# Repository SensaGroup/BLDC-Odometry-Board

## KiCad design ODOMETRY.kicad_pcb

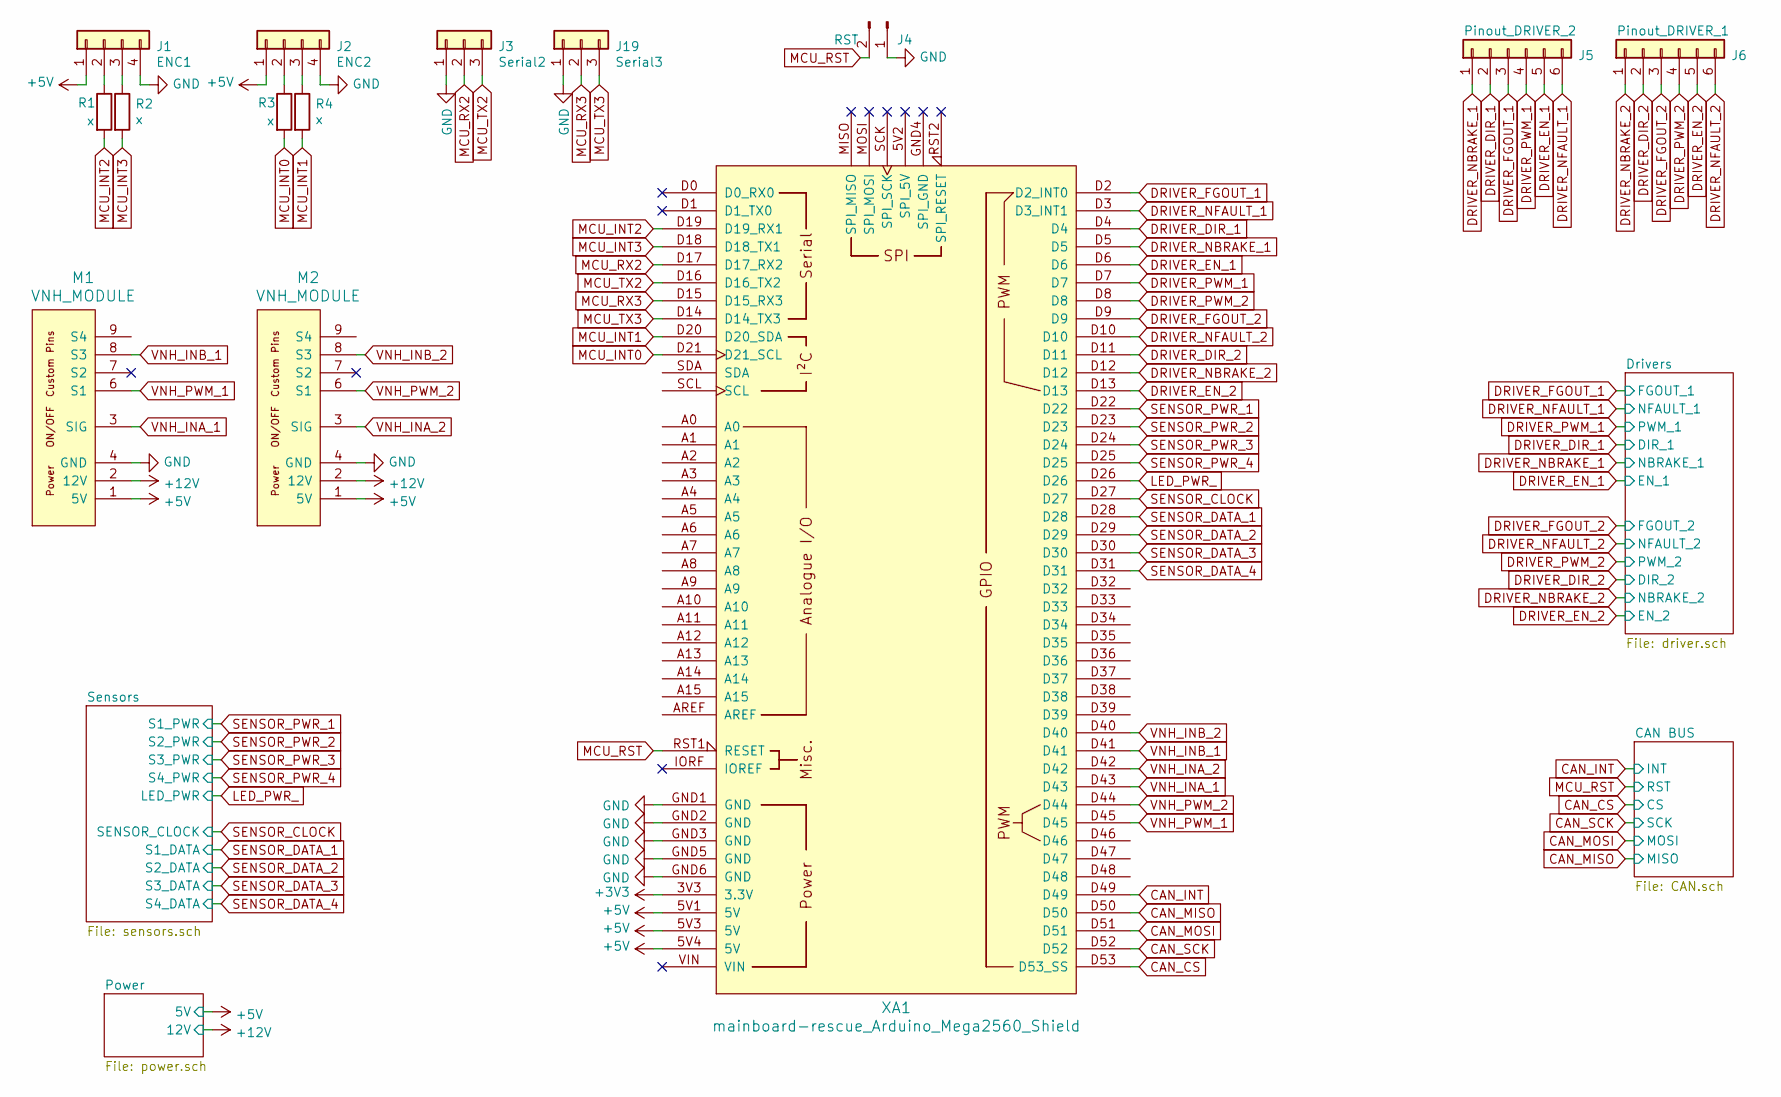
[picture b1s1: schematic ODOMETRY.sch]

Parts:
J1: ENC1; PinHeader_1x04_P2.54mm_Vertical
J2: ENC2; PinHeader_1x04_P2.54mm_Vertical
J3: Serial2; JST_PH_B3B-PH-K_1x03_P2.00mm_Vertical
J4: RST; PinHeader_1x02_P2.00mm_Vertical
J5: Pinout_DRIVER_2; PinHeader_1x06_P2.00mm_Vertical
J6: Pinout_DRIVER_1; PinHeader_1x06_P2.00mm_Vertical
J19: Serial3; JST_PH_B3B-PH-K_1x03_P2.00mm_Vertical
M1, M2: VNH_MODULE; Aktuator_Module
R1, R2, R3, R4: x; R_0603_1608Metric
XA1: mainboard-rescue_Arduino_Mega2560_Shield; Arduino_Mega2560_Shield

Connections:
+3V3: XA1.3V3 (3.3V)
+5V: J1.1, J2.1, M1.1 (5V), M2.1 (5V), XA1.5V1 (5V), XA1.5V3 (5V), XA1.5V4 (5V); also elsewhere on the board
CAN_CS: XA1.D53 (D53_SS); also elsewhere on the board
CAN_INT: XA1.D49; also elsewhere on the board
CAN_MISO: XA1.D50; also elsewhere on the board
CAN_MOSI: XA1.D51; also elsewhere on the board
CAN_SCK: XA1.D52; also elsewhere on the board
DIR_1: J5.2, XA1.D4; also elsewhere on the board
DIR_2: J6.2, XA1.D11; also elsewhere on the board
DRIVER_EN_1: J5.5, XA1.D6; also elsewhere on the board
DRIVER_EN_2: J6.5, XA1.D13; also elsewhere on the board
DRIVER_FGOUT_1: J5.3, XA1.D2 (D2_INT0); also elsewhere on the board
DRIVER_FGOUT_2: J6.3, XA1.D9; also elsewhere on the board
DRIVER_NBRAKE_1: J5.1, XA1.D5; also elsewhere on the board
DRIVER_NBRAKE_2: J6.1, XA1.D12; also elsewhere on the board
DRIVER_NFAULT_1: J5.6, XA1.D3 (D3_INT1); also elsewhere on the board
DRIVER_NFAULT_2: J6.6, XA1.D10; also elsewhere on the board
DRIVER_PWM_1: J5.4, XA1.D7; also elsewhere on the board
DRIVER_PWM_2: J6.4, XA1.D8; also elsewhere on the board
GND: J1.4, J2.4, J3.1, J4.1, J19.1, M1.4 (GND), M2.4 (GND), XA1.GND1 (GND), XA1.GND2 (GND), XA1.GND3 (GND), XA1.GND5 (GND), XA1.GND6 (GND); also elsewhere on the board
LED_PWR_: XA1.D26; also elsewhere on the board
MCU_INT0: R3.2, XA1.D21 (D21_SCL)
MCU_INT1: R4.2, XA1.D20 (D20_SDA)
MCU_INT2: R1.2, XA1.D19 (D19_RX1)
MCU_INT3: R2.2, XA1.D18 (D18_TX1)
MCU_RST: J4.2, XA1.RST1 (RESET); also elsewhere on the board
MCU_RX2: J3.2, XA1.D17 (D17_RX2)
MCU_RX3: J19.2, XA1.D15 (D15_RX3)
MCU_TX2: J3.3, XA1.D16 (D16_TX2)
MCU_TX3: J19.3, XA1.D14 (D14_TX3)
unnamed: J1.2, R1.1
unnamed: J1.3, R2.1
unnamed: J2.2, R3.1
unnamed: J2.3, R4.1
SENSOR_CLOCK: XA1.D27; also elsewhere on the board
SENSOR_DATA_1: XA1.D28; also elsewhere on the board
SENSOR_DATA_2: XA1.D29; also elsewhere on the board
SENSOR_DATA_3: XA1.D30; also elsewhere on the board
SENSOR_DATA_4: XA1.D31; also elsewhere on the board
SENSOR_PWR_1: XA1.D22; also elsewhere on the board
SENSOR_PWR_2: XA1.D23; also elsewhere on the board
SENSOR_PWR_3: XA1.D24; also elsewhere on the board
SENSOR_PWR_4: XA1.D25; also elsewhere on the board
VDRAIN_1: M1.2 (12V), M2.2 (12V); also elsewhere on the board
VNH_INA_1: M1.3 (SIG), XA1.D43
VNH_INA_2: M2.3 (SIG), XA1.D42
VNH_INB_1: M1.8 (S3), XA1.D41
VNH_INB_2: M2.8 (S3), XA1.D40
VNH_PWM_1: M1.6 (S1), XA1.D45
VNH_PWM_2: M2.6 (S1), XA1.D44

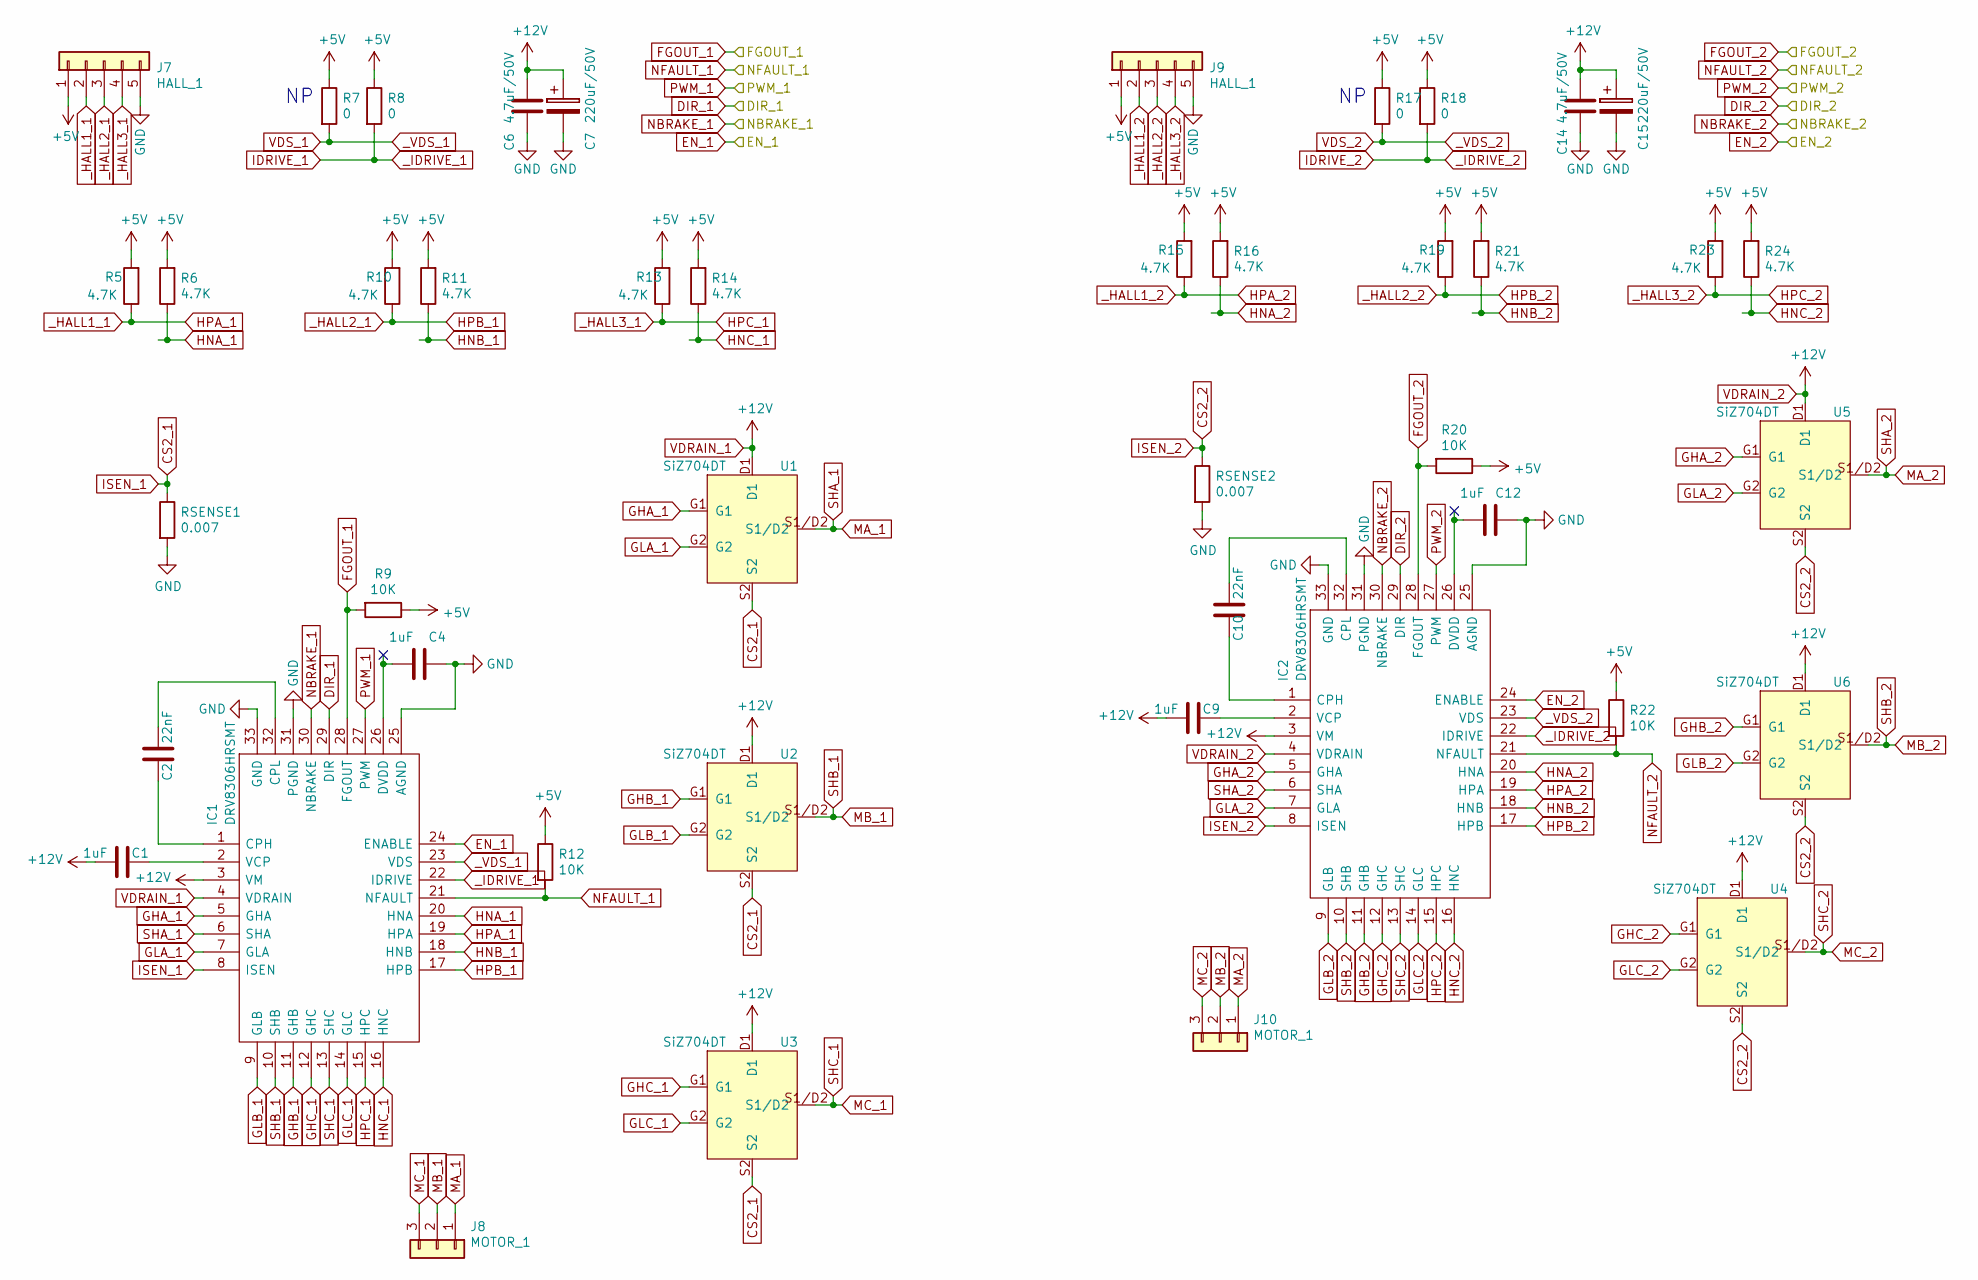
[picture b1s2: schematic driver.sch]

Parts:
C1, C4, C9, C12: 1uF; C_0603_1608Metric
C2, C10: 22nF; C_0603_1608Metric
C6, C14: 4.7uF/50V; C_1206_3216Metric
C7, C15: 220uF/50V; C_Elec_10x10.2
IC1, IC2: DRV8306HRSMT; QFN40P400X400X100-33N-D; Manufacturer_Part_Number DRV8306HRSMT; Mouser Part Number 595-DRV8306HRSMT
J7, J9: HALL_1; PinHeader_1x05_P2.54mm_Vertical
J8, J10: MOTOR_1; TerminalBlock_Phoenix_MKDS-1,5-3_1x03_P5.00mm_Horizontal
R5, R6, R10, R11, R13, R14, R15, R16, R19, R21, R23, R24: 4.7K; R_0603_1608Metric
R7, R8, R17, R18: 0; R_0603_1608Metric
R9, R12, R20, R22: 10K; R_0603_1608Metric
RSENSE1, RSENSE2: 0.007; R_2512_6332Metric
U1, U2, U3, U4, U5, U6: SiZ704DT

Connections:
+5V: J7.1, J9.1, R5.2, R6.2, R7.1, R8.1, R9.1, R10.2, R11.2, R12.1, R13.2, R14.2, R15.2, R16.2, R17.1, R18.1, R19.2, R20.1, R21.2, R22.1, R23.2, R24.2; also elsewhere on the board
CS2_1: IC1.8 (ISEN), RSENSE1.1, U1.S2, U2.S2, U3.S2
CS2_2: IC2.8 (ISEN), RSENSE2.1, U4.S2, U5.S2, U6.S2
DIR_1: IC1.29 (DIR); also elsewhere on the board
DIR_2: IC2.29 (DIR); also elsewhere on the board
DRIVER_EN_1: IC1.24 (ENABLE); also elsewhere on the board
DRIVER_EN_2: IC2.24 (ENABLE); also elsewhere on the board
DRIVER_FGOUT_1: IC1.28 (FGOUT), R9.2; also elsewhere on the board
DRIVER_FGOUT_2: IC2.28 (FGOUT), R20.2; also elsewhere on the board
DRIVER_NBRAKE_1: IC1.30 (NBRAKE); also elsewhere on the board
DRIVER_NBRAKE_2: IC2.30 (NBRAKE); also elsewhere on the board
DRIVER_NFAULT_1: IC1.21 (NFAULT), R12.2; also elsewhere on the board
DRIVER_NFAULT_2: IC2.21 (NFAULT), R22.2; also elsewhere on the board
DRIVER_PWM_1: IC1.27 (PWM); also elsewhere on the board
DRIVER_PWM_2: IC2.27 (PWM); also elsewhere on the board
GHA_1: IC1.5 (GHA), U1.G1
GHA_2: IC2.5 (GHA), U5.G1
GHB_1: IC1.11 (GHB), U2.G1
GHB_2: IC2.11 (GHB), U6.G1
GHC_1: IC1.12 (GHC), U3.G1
GHC_2: IC2.12 (GHC), U4.G1
GLA_1: IC1.7 (GLA), U1.G2
GLA_2: IC2.7 (GLA), U5.G2
GLB_1: IC1.9 (GLB), U2.G2
GLB_2: IC2.9 (GLB), U6.G2
GLC_1: IC1.14 (GLC), U3.G2
GLC_2: IC2.14 (GLC), U4.G2
GND: C4.1, C6.1, C7.2, C12.1, C14.1, C15.2, IC1.25 (AGND), IC1.31 (PGND), IC1.33 (GND), IC2.25 (AGND), IC2.31 (PGND), IC2.33 (GND), J7.5, J9.5, RSENSE1.2, RSENSE2.2; also elsewhere on the board
HNA_1: IC1.20 (HNA), R6.1
HNA_2: IC2.20 (HNA), R16.1
HNB_1: IC1.18 (HNB), R11.1
HNB_2: IC2.18 (HNB), R21.1
HNC_1: IC1.16 (HNC), R14.1
HNC_2: IC2.16 (HNC), R24.1
HPA_1: IC1.19 (HPA), J7.2, R5.1
HPA_2: IC2.19 (HPA), J9.2, R15.1
HPB_1: IC1.17 (HPB), J7.3, R10.1
HPB_2: IC2.17 (HPB), J9.3, R19.1
HPC_1: IC1.15 (HPC), J7.4, R13.1
HPC_2: IC2.15 (HPC), J9.4, R23.1
IDRIVE_1: IC1.22 (IDRIVE), R8.2
IDRIVE_2: IC2.22 (IDRIVE), R18.2
MA_1: IC1.6 (SHA), J8.1, U1.S1/D2
MA_2: IC2.6 (SHA), J10.1, U5.S1/D2
MB_1: IC1.10 (SHB), J8.2, U2.S1/D2
MB_2: IC2.10 (SHB), J10.2, U6.S1/D2
MC_1: IC1.13 (SHC), J8.3, U3.S1/D2
MC_2: IC2.13 (SHC), J10.3, U4.S1/D2
unnamed: C1.1, IC1.2 (VCP)
unnamed: C2.1, IC1.1 (CPH)
unnamed: C2.2, IC1.32 (CPL)
unnamed: C4.2, IC1.26 (DVDD)
unnamed: C9.1, IC2.2 (VCP)
unnamed: C10.1, IC2.1 (CPH)
unnamed: C10.2, IC2.32 (CPL)
unnamed: C12.2, IC2.26 (DVDD)
VDRAIN_1: C1.2, C6.2, C7.1, C9.2, C14.2, C15.1, IC1.3 (VM), IC1.4 (VDRAIN), IC2.3 (VM), IC2.4 (VDRAIN), U1.D1, U2.D1, U3.D1, U4.D1, U5.D1, U6.D1; also elsewhere on the board
VDS_1: IC1.23 (VDS), R7.2
VDS_2: IC2.23 (VDS), R17.2

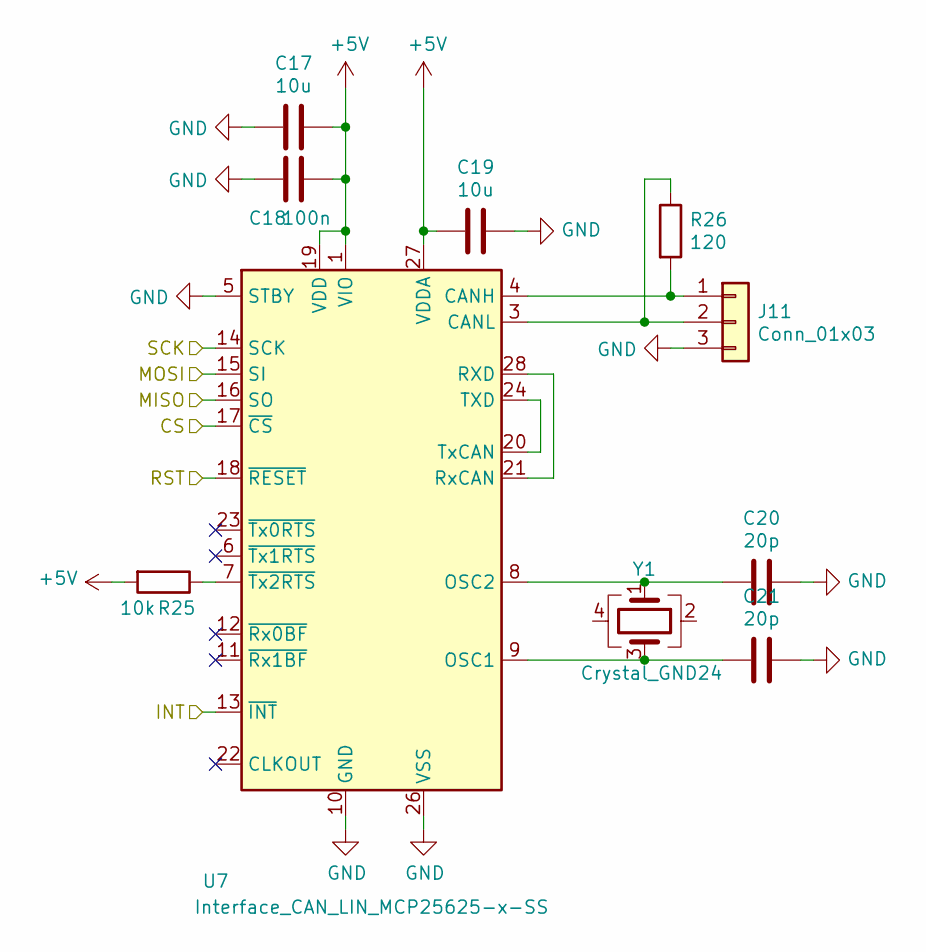
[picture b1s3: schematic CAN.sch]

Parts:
C17, C19: 10u; C_0603_1608Metric
C18: 100n; C_0603_1608Metric
C20, C21: 20p; C_0603_1608Metric
J11: Conn_01x03; JST_PH_B3B-PH-K_1x03_P2.00mm_Vertical
R25: 10k; R_0603_1608Metric
R26: 120; R_0603_1608Metric
U7: Interface_CAN_LIN_MCP25625-x-SS; SSOP-28_5.3x10.2mm_P0.65mm
Y1: Crystal_GND24; Crystal_SMD_SeikoEpson_FA238-4Pin_3.2x2.5mm_HandSoldering

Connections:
+5V: C17.1, C18.1, C19.1, R25.2, U7.1 (VIO), U7.19 (VDD), U7.27 (VDDA); also elsewhere on the board
CAN_CS: U7.17 (~CS); also elsewhere on the board
CAN_INT: U7.13 (~INT); also elsewhere on the board
CAN_MISO: U7.16 (SO); also elsewhere on the board
CAN_MOSI: U7.15 (SI); also elsewhere on the board
CAN_SCK: U7.14 (SCK); also elsewhere on the board
GND: C17.2, C18.2, C19.2, C20.2, C21.2, J11.3, U7.5 (STBY), U7.10 (GND), U7.26 (VSS); also elsewhere on the board
MCU_RST: U7.18 (~RESET); also elsewhere on the board
unnamed: C20.1, U7.8 (OSC2), Y1.1
unnamed: C21.1, U7.9 (OSC1), Y1.3
unnamed: J11.1, R26.2, U7.4 (CANH)
unnamed: J11.2, R26.1, U7.3 (CANL)
unnamed: R25.1, U7.7 (~Tx2RTS)
unnamed: U7.20 (TxCAN), U7.24 (TXD)
unnamed: U7.21 (RxCAN), U7.28 (RXD)

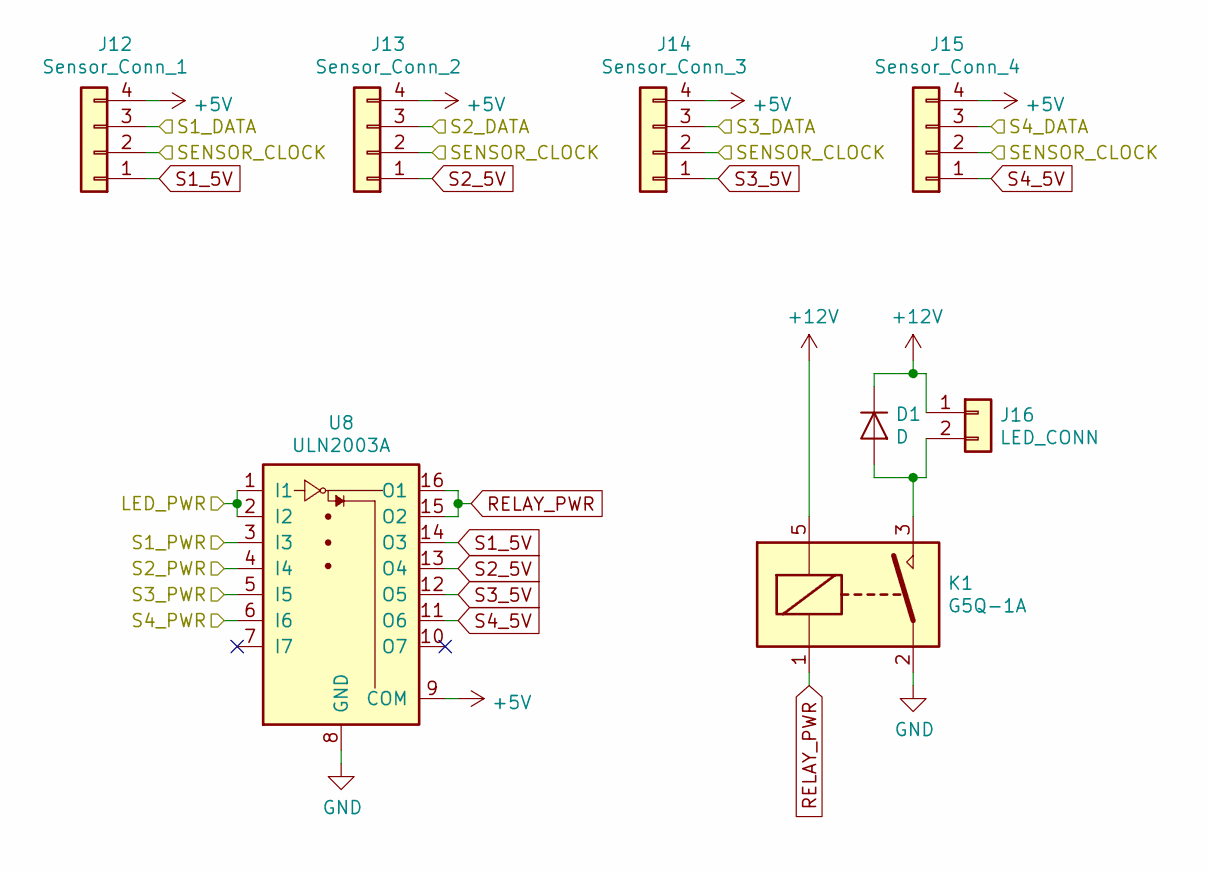
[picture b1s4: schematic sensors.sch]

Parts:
D1: D; D_SMA
J12: Sensor_Conn_1; JST_PH_B4B-PH-K_1x04_P2.00mm_Vertical
J13: Sensor_Conn_2; JST_PH_B4B-PH-K_1x04_P2.00mm_Vertical
J14: Sensor_Conn_3; JST_PH_B4B-PH-K_1x04_P2.00mm_Vertical
J15: Sensor_Conn_4; JST_PH_B4B-PH-K_1x04_P2.00mm_Vertical
J16: LED_CONN; JST_PH_B2B-PH-K_1x02_P2.00mm_Vertical
K1: G5Q-1A; Relay_SPST_Omron-G5Q-1A
U8: ULN2003A; TSSOP-16-1EP_4.4x5mm_P0.65mm

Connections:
+5V: J12.4, J13.4, J14.4, J15.4, U8.9 (COM); also elsewhere on the board
GND: K1.2, U8.8 (GND); also elsewhere on the board
LED_PWR_: U8.1 (I1), U8.2 (I2); also elsewhere on the board
unnamed: D1.2 (A), J16.2, K1.3
RELAY_PWR: K1.1, U8.15 (O2), U8.16 (O1)
S1_5V: J12.1, U8.14 (O3)
S2_5V: J13.1, U8.13 (O4)
S3_5V: J14.1, U8.12 (O5)
S4_5V: J15.1, U8.11 (O6)
SENSOR_CLOCK: J12.2, J13.2, J14.2, J15.2; also elsewhere on the board
SENSOR_DATA_1: J12.3; also elsewhere on the board
SENSOR_DATA_2: J13.3; also elsewhere on the board
SENSOR_DATA_3: J14.3; also elsewhere on the board
SENSOR_DATA_4: J15.3; also elsewhere on the board
SENSOR_PWR_1: U8.3 (I3); also elsewhere on the board
SENSOR_PWR_2: U8.4 (I4); also elsewhere on the board
SENSOR_PWR_3: U8.5 (I5); also elsewhere on the board
SENSOR_PWR_4: U8.6 (I6); also elsewhere on the board
VDRAIN_1: D1.1 (K), J16.1, K1.5; also elsewhere on the board

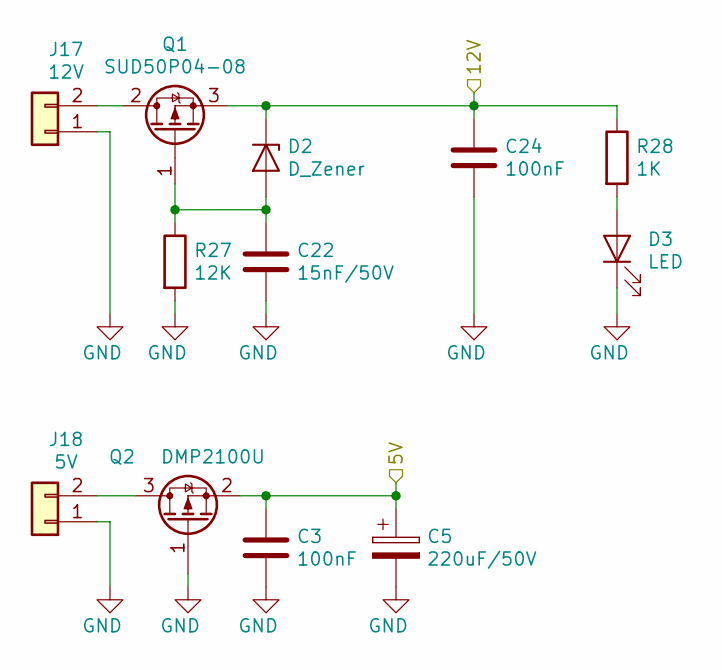
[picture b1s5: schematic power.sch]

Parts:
C3, C24: 100nF; C_0603_1608Metric
C5: 220uF/50V; C_Elec_10x10.2
C22: 15nF/50V; C_0603_1608Metric
D2: D_Zener; D_SOD-323_HandSoldering
D3: LED; LED_1206_3216Metric
J17: 12V; TerminalBlock_Phoenix_MKDS-1,5-2_1x02_P5.00mm_Horizontal
J18: 5V; TerminalBlock_Phoenix_MKDS-1,5-2_1x02_P5.00mm_Horizontal
Q1: SUD50P04-08; TO-252-2
Q2: DMP2100U; SOT-23
R27: 12K; R_0603_1608Metric
R28: 1K; C_0603_1608Metric

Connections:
+5V: C3.1, C5.1, Q2.2 (S); also elsewhere on the board
GND: C3.2, C5.2, C22.2, C24.2, D3.1 (K), J17.1, J18.1, Q2.1 (G), R27.2; also elsewhere on the board
unnamed: C22.1, D2.2 (A), Q1.1 (G), R27.1
unnamed: D3.2 (A), R28.2
unnamed: J17.2, Q1.2 (D)
unnamed: J18.2, Q2.3 (D)
VDRAIN_1: C24.1, D2.1 (K), Q1.3 (S), R28.1; also elsewhere on the board

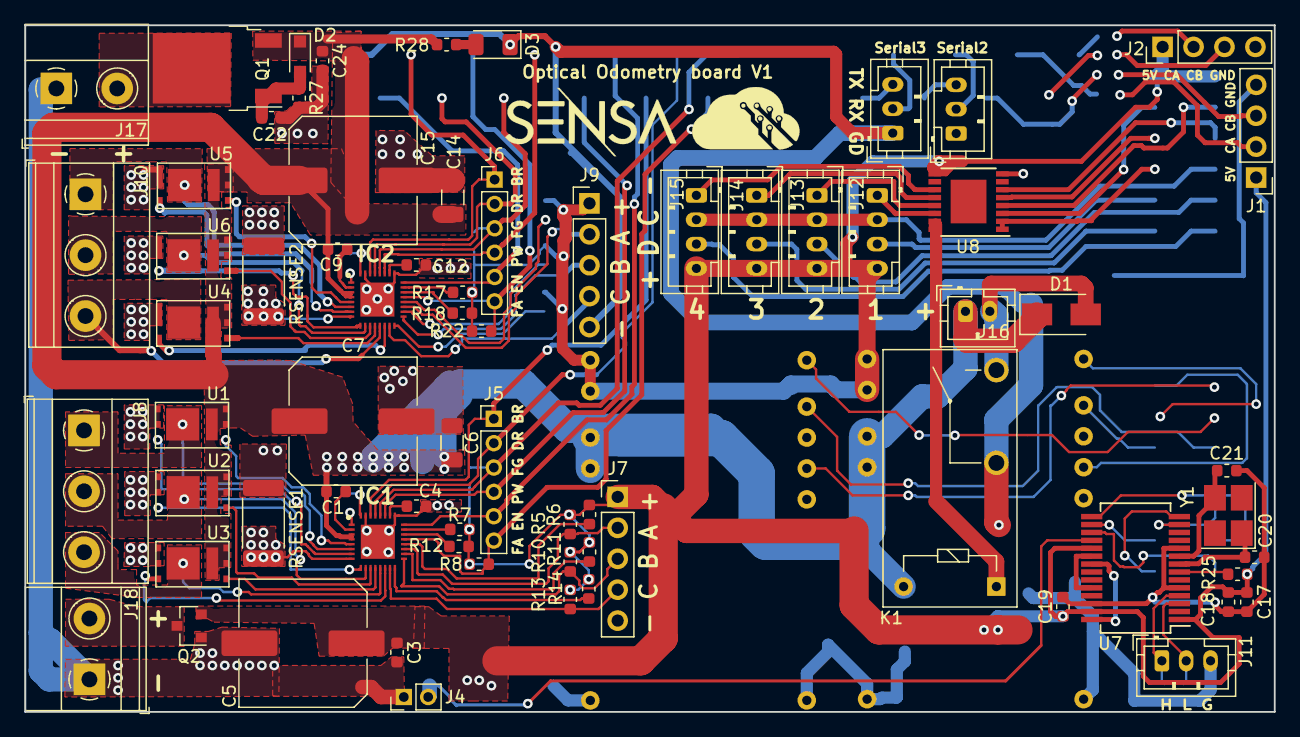
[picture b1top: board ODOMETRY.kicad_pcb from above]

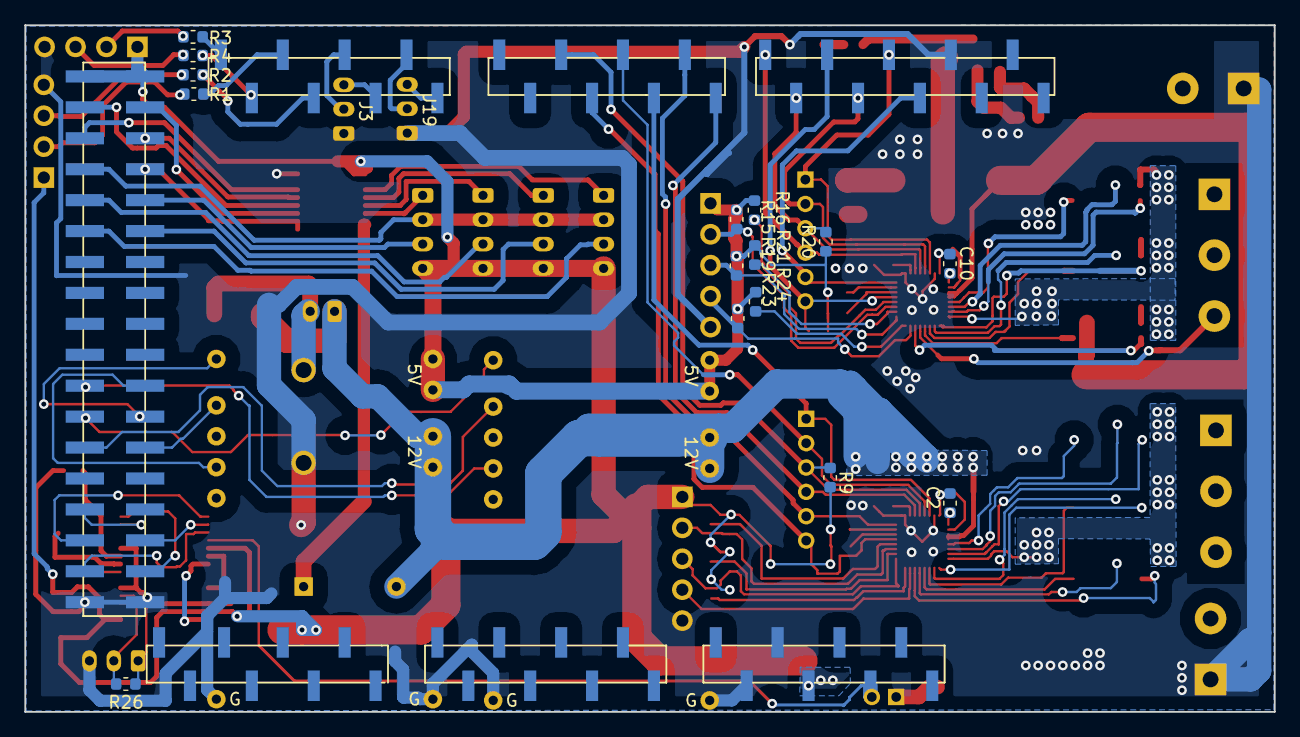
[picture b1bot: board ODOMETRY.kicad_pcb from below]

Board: 2 copper layers, 102.6 x 56.4 mm, 88 parts (15 on the bottom side), 110 nets.

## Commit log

2019-09-07 added readme
